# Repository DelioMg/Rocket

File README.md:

# Mini Foguete

Projeto de desenvolvimento de um Minifoguete com Base em Sistemas de Massa Variável para Materia de Fisica Experimental A.
 
O projeto consiste em uma abordagem sistemática para o desenvolvimento e aprimoramento de foguetes em miniatura, utilizando uma metodologia que envolve aquisição de dados, cálculo de velocidade do foguete e comparação com dados reais obtidos durante os testes com intenção de demonstrar o funcionamento do momento linear em um sistema de massas variáveis. O projeto consiste na obtenção de propelente para realizar teste e através dos dados obtidos calcular velocidade que o foguete pode atingir que após esses será realizado o lançamento de mini foguete e obtenção dos dados de voo para comparação com resultado obtido com cálculo.  

Etapas :
1. Aquisição do Motor. 
2. Teste Estático do Motor
3. Desenvolvimento de uma Avionica para aferição da Altitude.
4. Desenvolvimento do Minifoguete: Utilizando um modelo 3D como base com ajuste para acomodar uma aviônica.
5. Com Massa do Minifoguete Calcular a Velocidade.
6. Lançar o Foguete.
7. Comparar os Dados.

## 1. Motor.

Por já ter conhecimento na produção do motor não foi preciso comprar, em que foi produzido KNSu e a carcaça do motor feita com cano de PVC de 3/4.

## 2. Teste Estatico 

Para realização do Teste estatico foi utilizada uma celula de carga de 10Kg com Hz711 modificado para 80hz para melhor precisão das leituras obtendo os resultados Abaixo:

## 3.Avionica 

Nesta etapa do projeto, foi desenvolvida uma PCB utilizando o software Eagle. A PCB tem como objetivo realizar a aferição da altitude durante o voo e envio dos dados para uma base remota. A placa utiliza componentes específicos para cada função, como o microcontrolador ESP8266 para cálculos, o sensor BMP280 para medição de altitude e temperatura, o sensor MPU6050 para medição de aceleração, o módulo NRF24L01+ para transmissão dos dados, um slot de Micro SD para funcionar como datalogger do voo, reguladores de tensão para ajustar a voltagem de 3,7V para 3,3V, um circuito para aferição da tensão da bateria, um circuito para acionar o paraquedas e um buzzer. Além disso, são utilizadas duas baterias de 3,7V para alimentação da placa.

## 4.Desenvolviemto do Minifoguete 

Nesta etapa do projeto, foi utilizado o modelo de foguete 3D Modular Model Rocket disponível no Thingiverse, que pode ser encontrado no seguinte link: [3D Modular Model Rocket](https://www.thingiverse.com/thing:8754).

Esse modelo de foguete foi modificado para permitir o acoplamento de diferentes tamanhos de motores. Além disso, o programa OpenRocket foi utilizado para ajustar a estabilidade do MiniFoguete.

## 5.Calculos

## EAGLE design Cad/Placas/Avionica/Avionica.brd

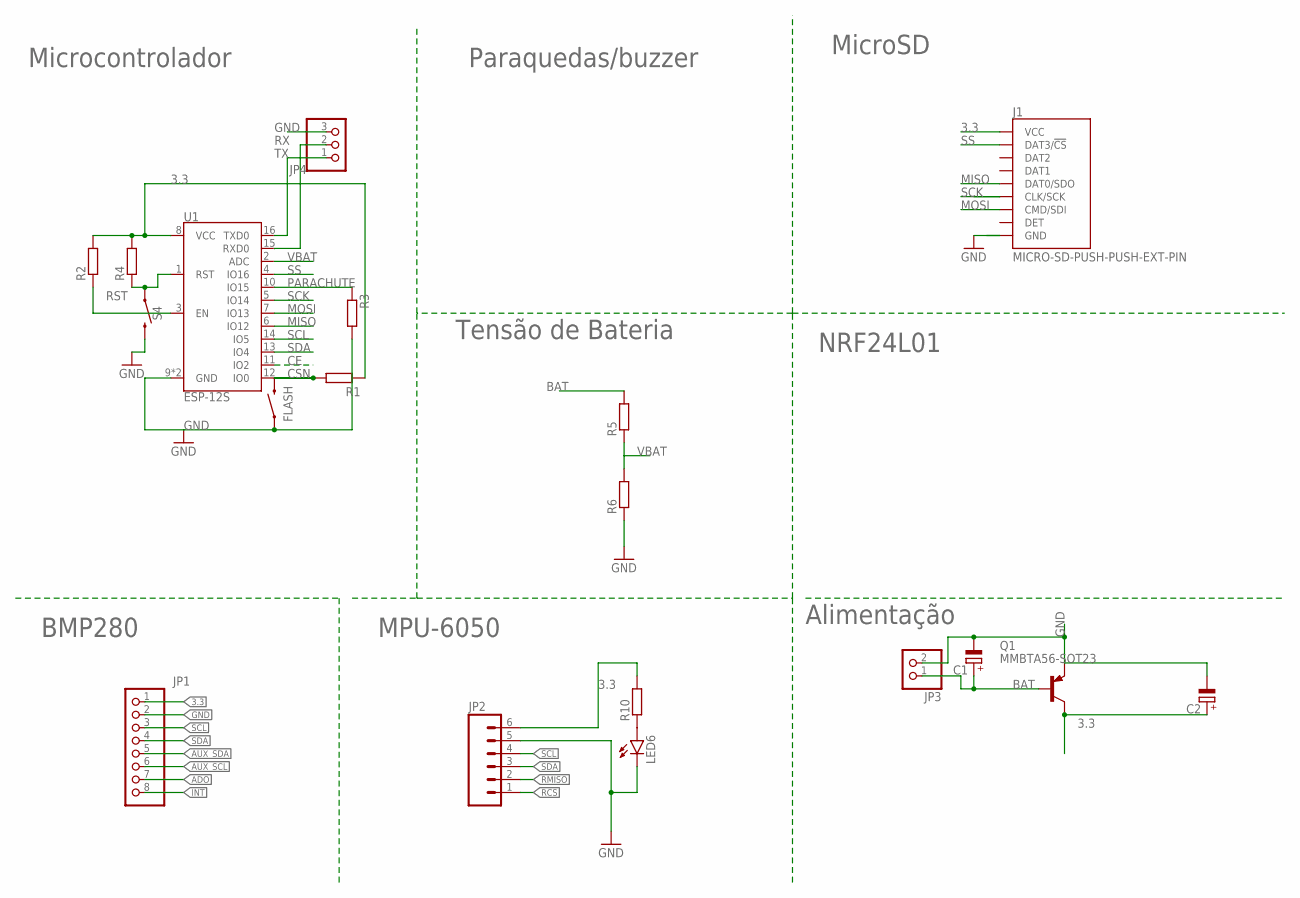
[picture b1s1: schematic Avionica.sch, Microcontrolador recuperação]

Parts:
C1, C2: CPOL-EUE1.8-4; E1,8-4
FLASH: MOMENTARY-SWITCH-SPST-SMD-5.2MM-TALL; TACTILE_SWITCH_SMD_5.2MM
J1: MICRO-SD-PUSH-PUSH-EXT-PIN; MICROSD-EXTERNALPIN
JP1: PINHD-1X8; 1X08
JP2: M06NO_SILK_FEMALE_PTH; 1X06_NO_SILK
JP3: PINHD-1X2; 1X02
JP4: PINHD-1X3; 1X03
LED6: LEDCHIP-LED0805; CHIP-LED0805
Q1: MMBTA56-SOT23; SOT23
R1, R2, R3, R4: R-EU_R0805W; R0805W
R5, R6, R10: R-EU_M0805; M0805
S4: MOMENTARY-SWITCH-SPST-SMD-5.2MM-TALL; TACTILE_SWITCH_SMD_5.2MM
U1: ESP-12S

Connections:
3.3: C2.+, J1.4 (VCC), JP1.1, JP2.6, Q1.3 (C), R1.2, R2.2, R4.2, R10.2, U1.8 (VCC)
ADO: JP1.7
AUX_SCL: JP1.6
AUX_SDA: JP1.5
BAT: C1.+, JP3.1, Q1.1 (B), R5.2
CE: U1.11 (IO2)
CSN: FLASH.3 (2), R1.1, U1.12 (IO0)
EN: R2.1, U1.3 (EN)
GND: C1.-, C2.-, FLASH.1, J1.6 (GND), J1.10 (GND), J1.11 (GND), J1.12 (GND), J1.13 (GND), JP1.2, JP2.5, JP3.2, JP4.3, LED6.C, Q1.2 (E), R3.2, R6.1, S4.3 (2), U1.9 (GND), U1.P$1 (GND)
INT: JP1.8
MISO: J1.7 (DAT0/SDO), U1.6 (IO12)
MOSI: J1.3 (CMD/SDI), U1.7 (IO13)
unnamed: LED6.A, R10.1
PARACHUTE: R3.1, U1.10 (IO15)
RCS: JP2.1
RMISO: JP2.2
RST: R4.1, S4.1, U1.1 (RST)
RX: JP4.2, U1.15 (RXD0)
SCK: J1.5 (CLK/SCK), U1.5 (IO14)
SCL: JP1.3, JP2.4, U1.14 (IO5)
SDA: JP1.4, JP2.3, U1.13 (IO4)
SS: J1.2 (DAT3/!CS!), U1.4 (IO16)
TX: JP4.1, U1.16 (TXD0)
VBAT: R5.1, R6.2, U1.2 (ADC)

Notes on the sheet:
BMP280
MPU-6050
Alimentação
MicroSD
Paraquedas/buzzer
Microcontrolador
Tensão de Bateria
NRF24L01

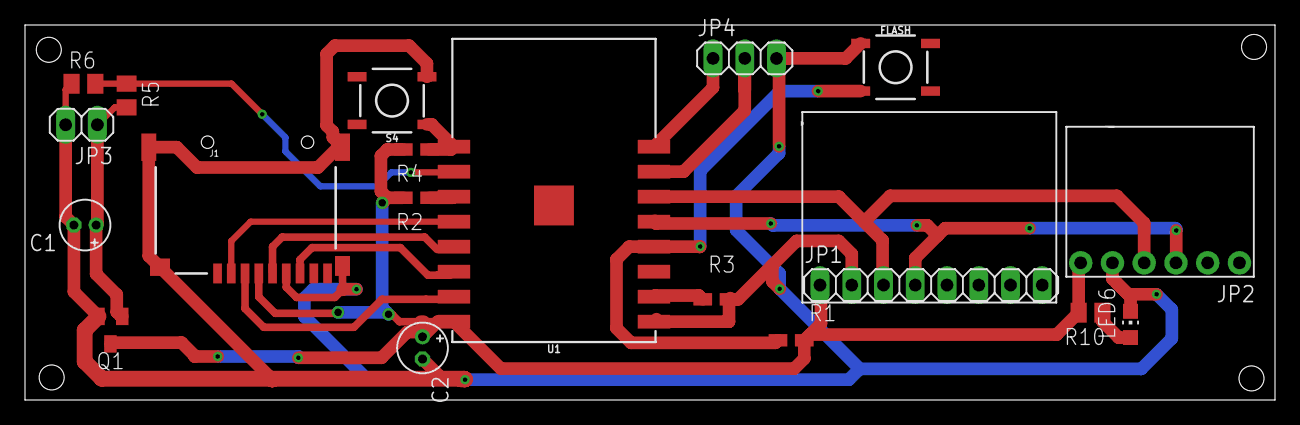
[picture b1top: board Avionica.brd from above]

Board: 2 copper layers, 100.0 x 30.0 mm, 19 parts (0 on the bottom side), 17 nets.

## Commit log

2023-06-03 Base
2023-06-05 codigos
2023-06-09 pcbs

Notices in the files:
parts and their libraries:
SparkFun-Connectors: Licensing: Creative Commons ShareAlike 4.0 International - https://creativecommons.org/licenses/by-sa/4.0
